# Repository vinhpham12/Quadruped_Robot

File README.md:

# Quadruped_Robot
A custom-designed 12-DOF quadruped robot platform featuring a modular 3D-printed chassis and a dedicated embedded controller board.

## Project Structure

* **hardware/**: 
  * `cad/`: Mechanical assembly, STEP files, and 3D printable STL files (SolidWorks).
  * `pcb/`: Custom mainboard schematics, PCB layout, and gerber files (KiCad).

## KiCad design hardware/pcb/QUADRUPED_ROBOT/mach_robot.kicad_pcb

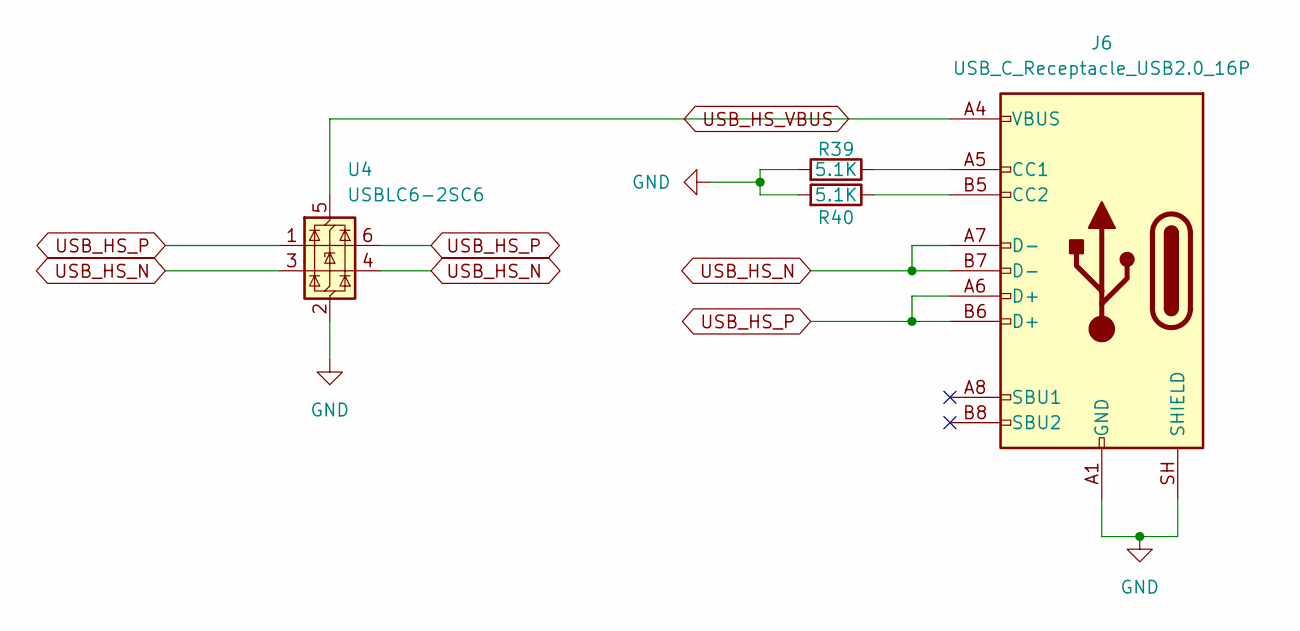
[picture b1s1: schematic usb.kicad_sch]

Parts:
J6: USB_C_Receptacle_USB2.0_16P; USB_C_Receptacle_Amphenol_12401948E412A
R39, R40: 5.1K; R_0805_2012Metric
U4: USBLC6-2SC6; SOT-23-6

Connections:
GND: J6.A1 (GND), J6.A12 (GND), J6.B1 (GND), J6.B12 (GND), J6.SH (SHIELD), R39.2, R40.2, U4.2 (GND); also elsewhere on the board
unnamed: J6.A5 (CC1), R39.1
unnamed: J6.B5 (CC2), R40.1
USB_HS_N: J6.A7 (D-), J6.B7 (D-), U4.3 (I/O2), U4.4 (I/O2); also elsewhere on the board
USB_HS_P: J6.A6 (D+), J6.B6 (D+), U4.1 (I/O1), U4.6 (I/O1); also elsewhere on the board
USB_HS_VBUS: J6.A4 (VBUS), J6.A9 (VBUS), J6.B4 (VBUS), J6.B9 (VBUS), U4.5 (VBUS); also elsewhere on the board

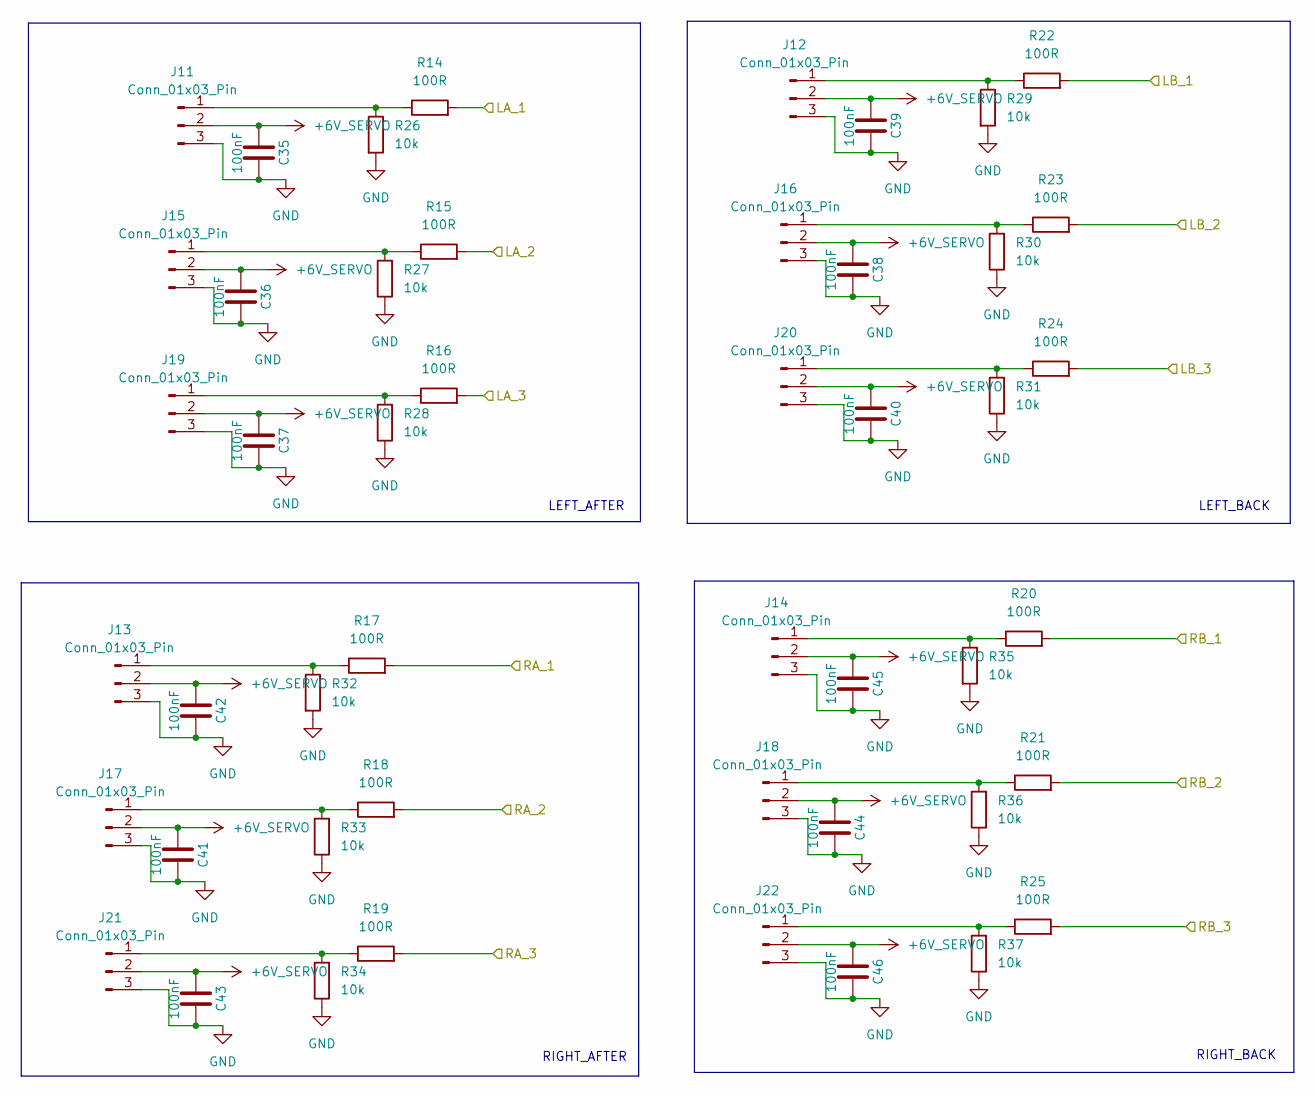
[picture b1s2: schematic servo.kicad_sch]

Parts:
C35, C36, C37, C38, C39, C40, C41, C42, C43, C44, C45, C46: 100nF; C_0805_2012Metric
J11, J12, J13, J14, J15, J16, J17, J18, J19, J20, J21, J22: Conn_01x03_Pin; PinHeader_1x03_P2.54mm_Vertical
R14, R15, R16, R17, R18, R19, R20, R21, R22, R23, R24, R25: 100R; R_0805_2012Metric
R26, R27, R28, R29, R30, R31, R32, R33, R34, R35, R36, R37: 10k; R_0805_2012Metric

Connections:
/chip/LA_1: R14.2; also elsewhere on the board
/chip/LA_2: R15.2; also elsewhere on the board
/chip/LA_3: R16.2; also elsewhere on the board
/chip/LB_1: R22.2; also elsewhere on the board
/chip/LB_2: R23.2; also elsewhere on the board
/chip/LB_3: R24.2; also elsewhere on the board
/chip/RA_1: R17.2; also elsewhere on the board
/chip/RA_2: R18.2; also elsewhere on the board
/chip/RA_3: R19.2; also elsewhere on the board
/chip/RB_1: R20.2; also elsewhere on the board
/chip/RB_2: R21.2; also elsewhere on the board
/chip/RB_3: R25.2; also elsewhere on the board
GND: C35.1, C36.1, C37.1, C38.1, C39.1, C40.1, C41.1, C42.1, C43.1, C44.1, C45.1, C46.1, J11.3, J12.3, J13.3, J14.3, J15.3, J16.3, J17.3, J18.3, J19.3, J20.3, J21.3, J22.3, R26.2, R27.1, R28.1, R29.2, R30.1, R31.1, R32.2, R33.1, R34.1, R35.2, R36.1, R37.1; also elsewhere on the board
unnamed: J11.1, R14.1, R26.1
unnamed: J12.1, R22.1, R29.1
unnamed: J13.1, R17.1, R32.1
unnamed: J14.1, R20.1, R35.1
unnamed: J15.1, R15.1, R27.2
unnamed: J16.1, R23.1, R30.2
unnamed: J17.1, R18.1, R33.2
unnamed: J18.1, R21.1, R36.2
unnamed: J19.1, R16.1, R28.2
unnamed: J20.1, R24.1, R31.2
unnamed: J21.1, R19.1, R34.2
unnamed: J22.1, R25.1, R37.2

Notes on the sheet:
LEFT_BACK
RIGHT_BACK
LEFT_AFTER
RIGHT_AFTER

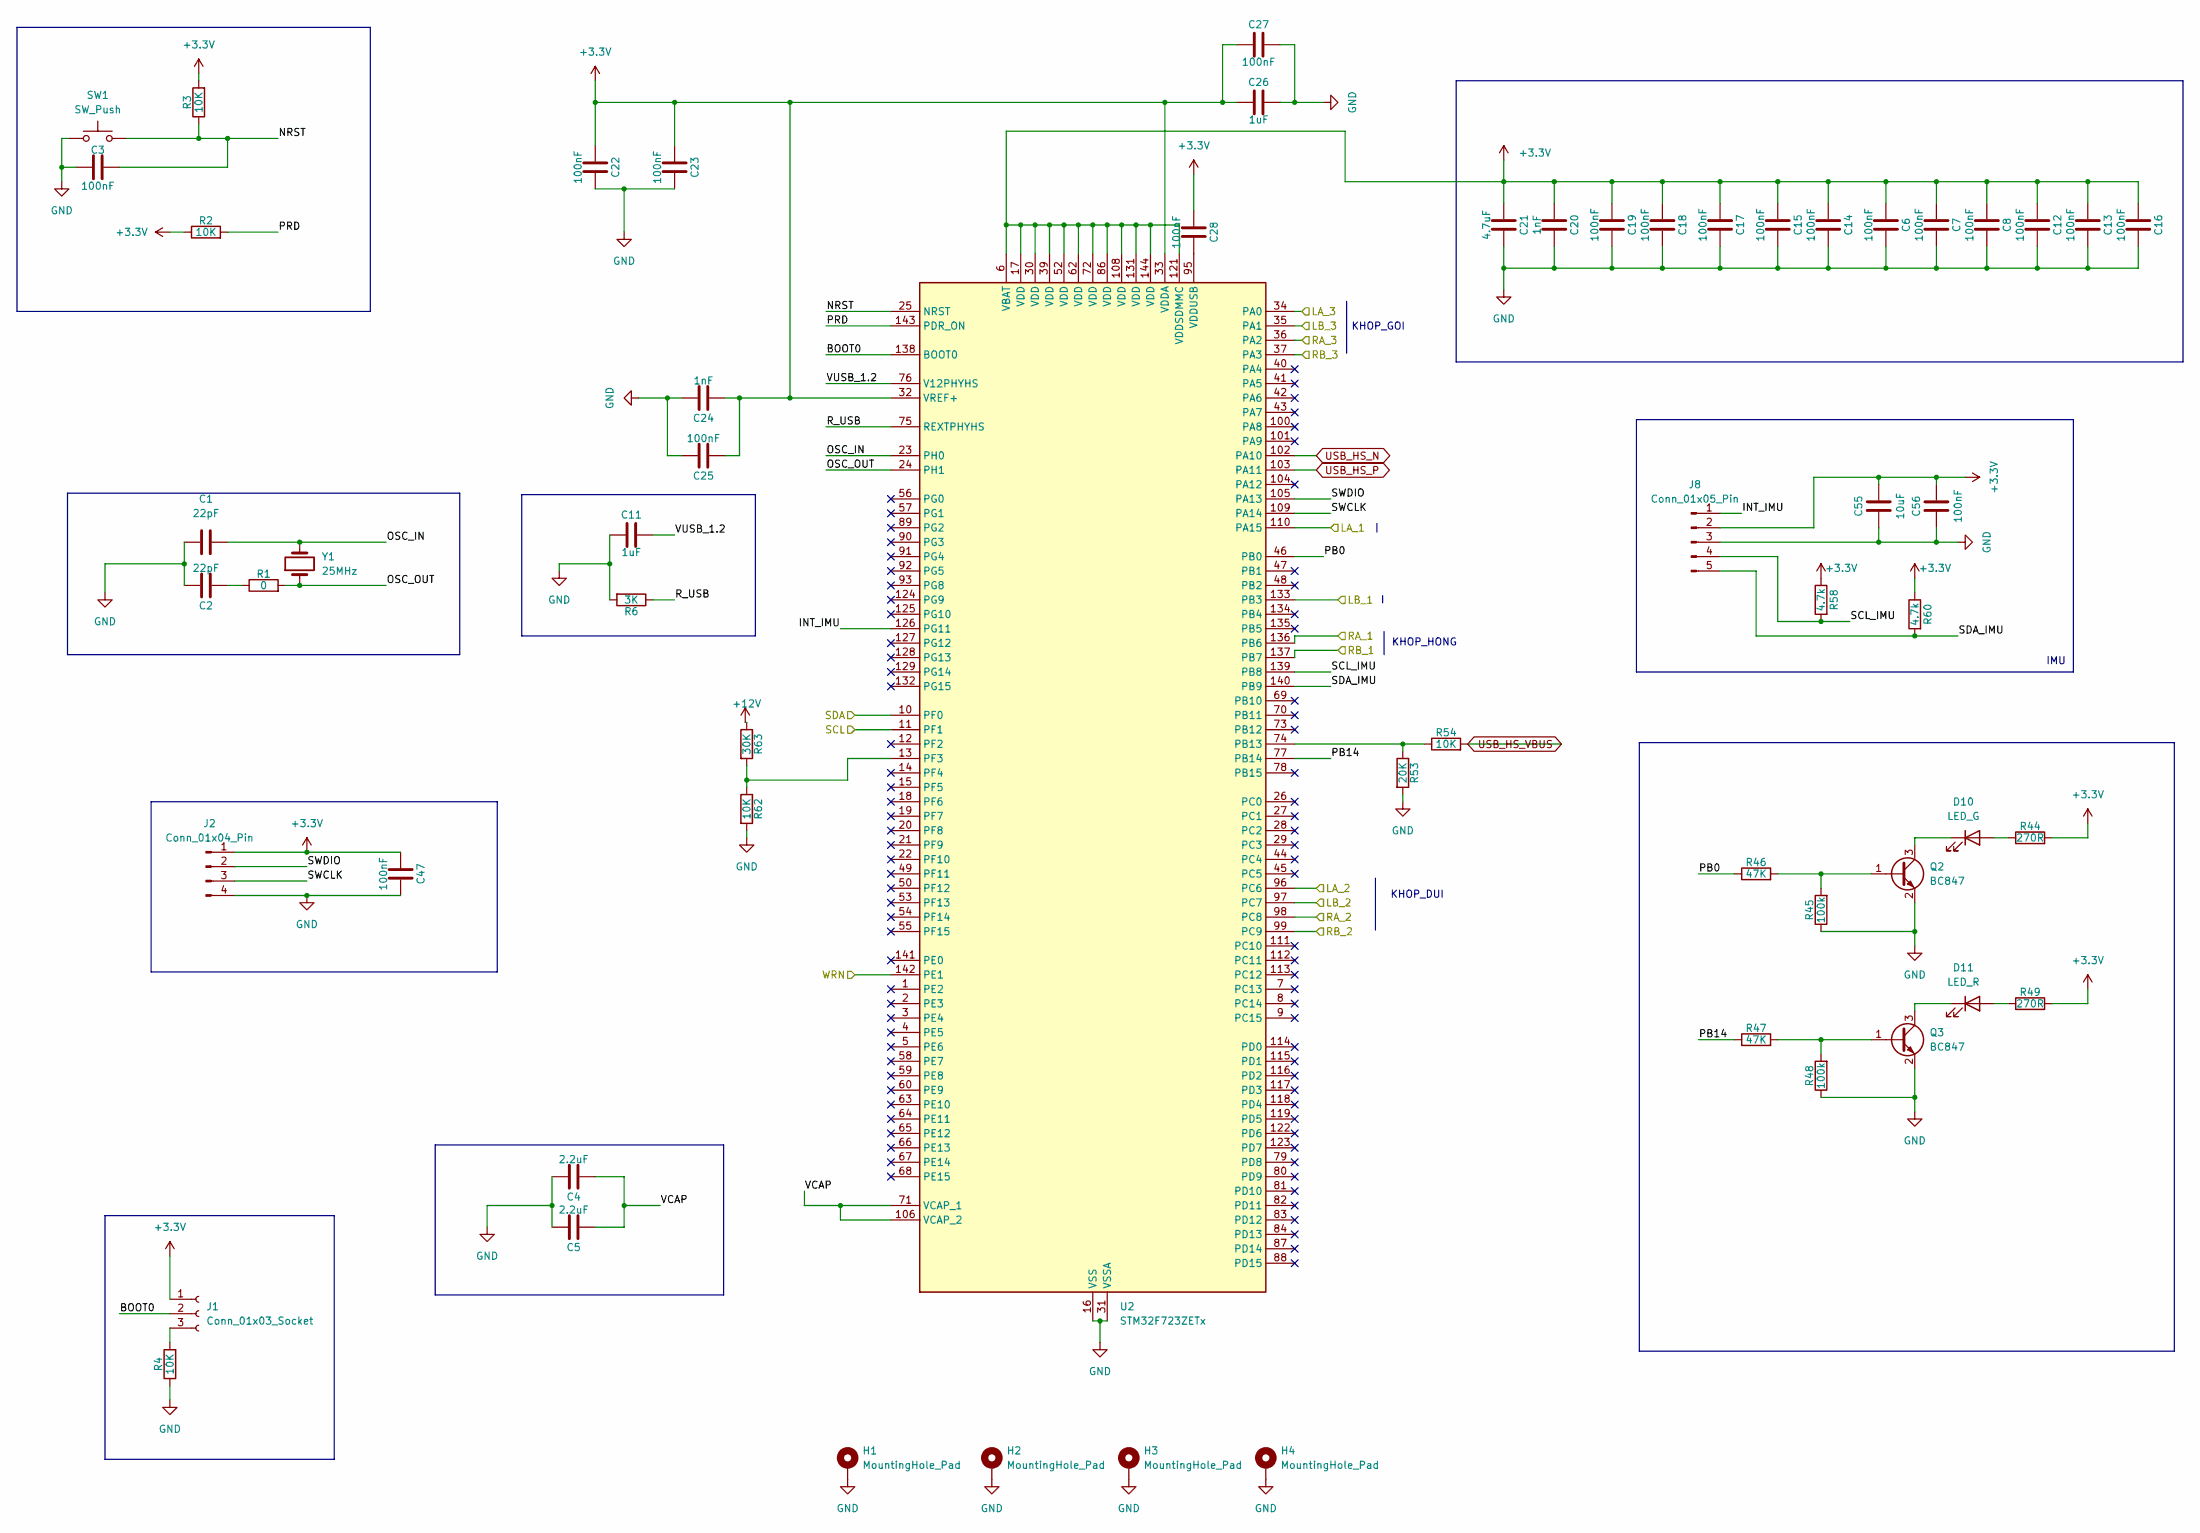
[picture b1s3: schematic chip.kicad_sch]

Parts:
C1, C2: 22pF; C_0805_2012Metric
C3, C6, C7, C8, C12, C13, C14, C15, C16, C17, C18, C19, C22, C23, C25, C27, C28, C47, C56: 100nF; C_0805_2012Metric
C4, C5: 2.2uF; C_0805_2012Metric
C11, C26: 1uF; C_0805_2012Metric
C20, C24: 1nF; C_0805_2012Metric
C21: 4.7uF; C_0805_2012Metric
C55: 10uF; C_0805_2012Metric
D10: LED_G; LED_0805_2012Metric
D11: LED_R; LED_0805_2012Metric
H1, H2, H3, H4: MountingHole_Pad; MountingHole_3.2mm_M3_Pad
J1: Conn_01x03_Socket; PinSocket_1x03_P2.54mm_Vertical
J2: Conn_01x04_Pin; PinSocket_1x04_P2.54mm_Vertical
J8: Conn_01x05_Pin; PinSocket_1x05_P2.54mm_Vertical
Q2, Q3: BC847; SOT-23
R1: 0; R_0805_2012Metric
R2, R3, R4, R54, R62: 10K; R_0805_2012Metric
R6: 3K; R_0805_2012Metric
R44, R49: 270R; R_0805_2012Metric
R45, R48: 100k; R_0805_2012Metric
R46, R47: 47K; R_0805_2012Metric
R53: 20K; R_0805_2012Metric
R58, R60: 4.7k; R_0805_2012Metric
R63: 30K; R_0805_2012Metric
SW1: SW_Push; SW_SMD_3x6mm
U2: STM32F723ZETx; LQFP-144_20x20mm_P0.5mm
Y1: 25MHz; Crystal_HC49-U_Vertical

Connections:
+3.3V: C6.2, C7.2, C8.2, C12.2, C13.2, C14.2, C15.2, C16.2, C17.2, C18.2, C19.2, C20.2, C21.2, C22.2, C23.2, C24.2, C25.2, C26.2, C27.2, C28.2, C47.2, C55.2, C56.2, J1.1, J2.1, J8.2, R2.1, R3.2, R44.2, R49.2, R58.1, R60.1, U2.6 (VBAT), U2.17 (VDD), U2.30 (VDD), U2.32 (VREF+), U2.33 (VDDA), U2.39 (VDD), U2.52 (VDD), U2.62 (VDD), U2.72 (VDD), U2.86 (VDD), U2.108 (VDD), U2.121 (VDDSDMMC), U2.131 (VDD), U2.144 (VDD); also elsewhere on the board
+12V: R63.1; also elsewhere on the board
/chip/BOOT0: J1.2, U2.138 (BOOT0)
/chip/INT_IMU: J8.1, U2.126 (PG11)
/chip/LA_1: U2.110 (PA15); also elsewhere on the board
/chip/LA_2: U2.96 (PC6); also elsewhere on the board
/chip/LA_3: U2.34 (PA0); also elsewhere on the board
/chip/LB_1: U2.133 (PB3); also elsewhere on the board
/chip/LB_2: U2.97 (PC7); also elsewhere on the board
/chip/LB_3: U2.35 (PA1); also elsewhere on the board
/chip/NRST: C3.2, R3.1, SW1.2, U2.25 (NRST)
/chip/OSC_IN: C1.2, U2.23 (PH0), Y1.2
/chip/OSC_OUT: R1.2, U2.24 (PH1), Y1.1
/chip/PB0: R46.1, U2.46 (PB0)
/chip/PB14: R47.1, U2.77 (PB14)
/chip/PRD: R2.2, U2.143 (PDR_ON)
/chip/RA_1: U2.136 (PB6); also elsewhere on the board
/chip/RA_2: U2.98 (PC8); also elsewhere on the board
/chip/RA_3: U2.36 (PA2); also elsewhere on the board
/chip/RB_1: U2.137 (PB7); also elsewhere on the board
/chip/RB_2: U2.99 (PC9); also elsewhere on the board
/chip/RB_3: U2.37 (PA3); also elsewhere on the board
/chip/R_USB: R6.1, U2.75 (REXTPHYHS)
/chip/SCL: U2.11 (PF1); also elsewhere on the board
/chip/SCL_IMU: J8.4, R58.2, U2.139 (PB8)
/chip/SDA: U2.10 (PF0); also elsewhere on the board
/chip/SDA_IMU: J8.5, R60.2, U2.140 (PB9)
/chip/SWCLK: J2.3, U2.109 (PA14)
/chip/SWDIO: J2.2, U2.105 (PA13)
/chip/VCAP: C4.2, C5.2, U2.71 (VCAP_1), U2.106 (VCAP_2)
/chip/VUSB_1.2: C11.1, U2.76 (V12PHYHS)
/chip/WRN: U2.142 (PE1); also elsewhere on the board
GND: C1.1, C2.1, C3.1, C4.1, C5.1, C6.1, C7.1, C8.1, C11.2, C12.1, C13.1, C14.1, C15.1, C16.1, C17.1, C18.1, C19.1, C20.1, C21.1, C22.1, C23.1, C24.1, C25.1, C26.1, C27.1, C47.1, C55.1, C56.1, H1.1 (1_1), H2.1 (1_1), H3.1 (1_1), H4.1 (1_1), J2.4, J8.3, Q2.2 (E), Q3.2 (E), R4.1, R6.2, R45.1, R48.1, R53.2, R62.2, SW1.1, U2.16 (VSS), U2.31 (VSSA), U2.38 (VSS), U2.51 (VSS), U2.61 (VSS), U2.85 (VSS), U2.94 (VSS), U2.107 (VSS), U2.120 (VSS), U2.130 (VSS); also elsewhere on the board
unnamed: C2.2, R1.1
unnamed: D10.2 (A), R44.1
unnamed: D10.1 (K), Q2.3 (C)
unnamed: D11.2 (A), R49.1
unnamed: D11.1 (K), Q3.3 (C)
unnamed: J1.3, R4.2
unnamed: Q2.1 (B), R45.2, R46.2
unnamed: Q3.1 (B), R47.2, R48.2
unnamed: R53.1, R54.1, U2.74 (PB13)
unnamed: R62.1, R63.2, U2.13 (PF3)
unnamed: C28.1, U2.95 (VDDUSB)
USB_HS_N: U2.102 (PA10); also elsewhere on the board
USB_HS_P: U2.103 (PA11); also elsewhere on the board
USB_HS_VBUS: R54.2; also elsewhere on the board

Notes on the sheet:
IMU
KHOP_HONG
KHOP_DUI
KHOP_GOI

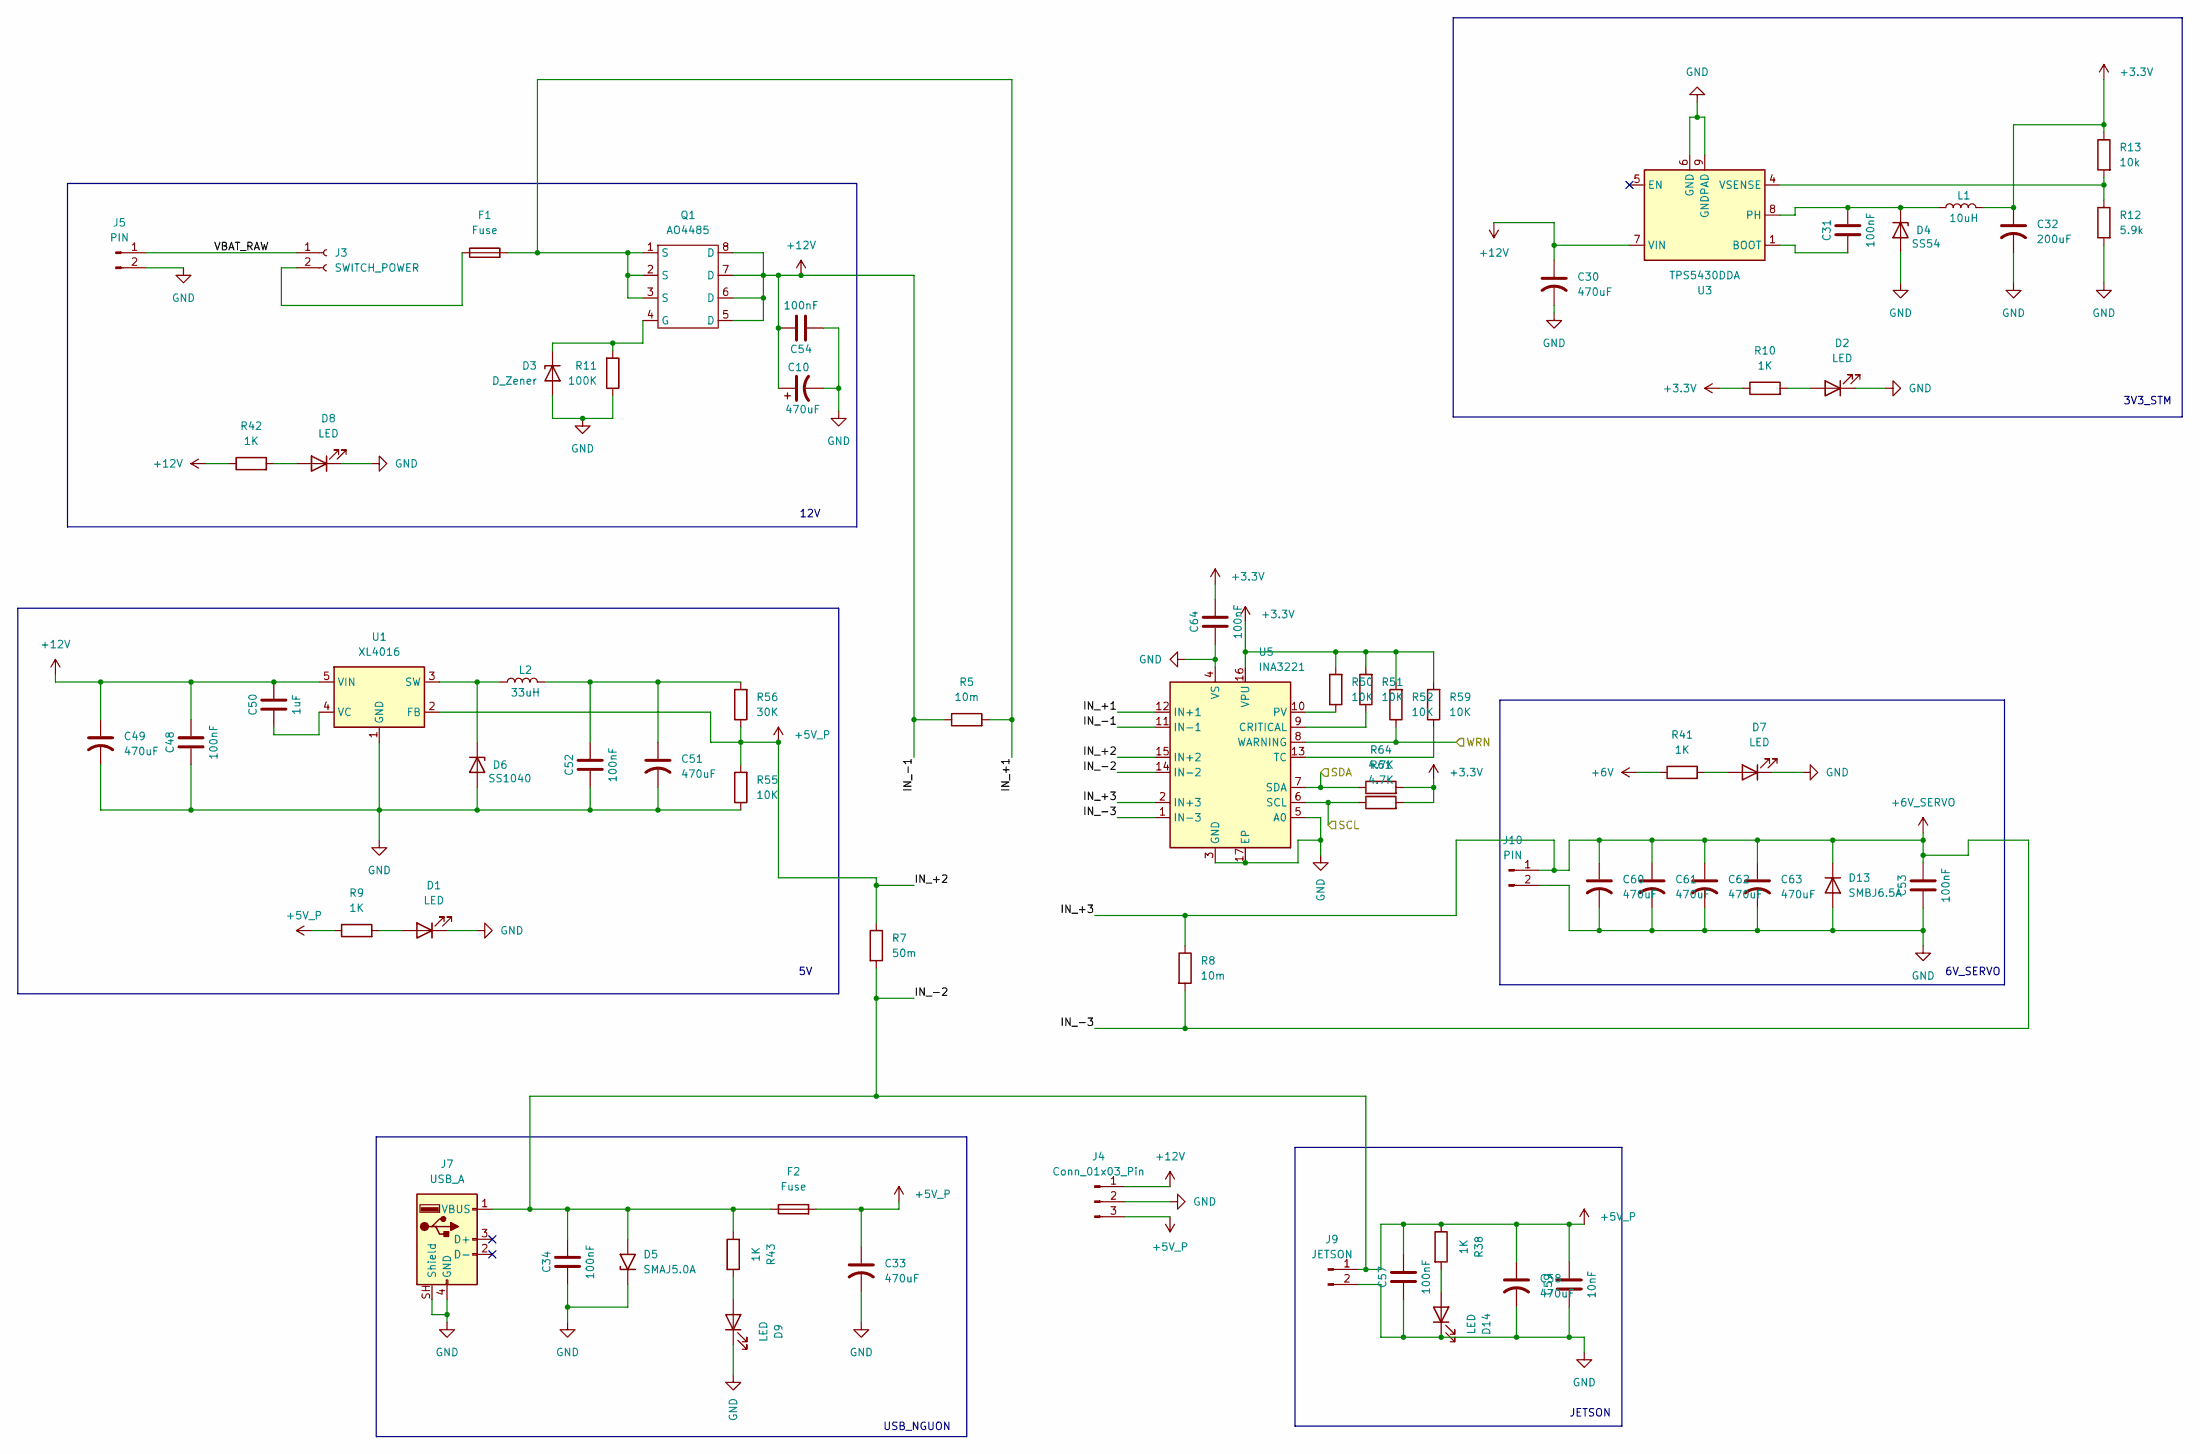
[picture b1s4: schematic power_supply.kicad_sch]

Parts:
C10: 470uF; CP_Radial_D10.0mm_P5.00mm
C30, C49, C51: 470uF; CP_Elec_8x10
C31, C34, C48, C52, C53, C54, C57, C64: 100nF; C_0805_2012Metric
C32: 200uF; CP_EIA-7343-31_Kemet-D_HandSolder
C33, C58, C60, C61, C62, C63: 470uF; CP_EIA-7343-31_Kemet-D_HandSolder
C50: 1uF; C_0805_2012Metric
C59: 10nF; C_0805_2012Metric
D1, D2, D7, D8, D9, D14: LED; LED_0805_2012Metric
D3: D_Zener; D_0805_2012Metric
D4: SS54; D_SMC
D5: SMAJ5.0A; D_SMA
D6: SS1040; D_SMC
D13: SMBJ6.5A; D_SMB
F1, F2: Fuse; Fuseholder_Littelfuse_100_series_5x20mm
J3: SWITCH_POWER; PinHeader_1x02_P2.54mm_Vertical
J4: Conn_01x03_Pin; PinHeader_1x03_P2.54mm_Vertical
J5, J10: PIN; TerminalBlock_Phoenix_MKDS-1,5-2-5.08_1x02_P5.08mm_Horizont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
J7: USB_A; USB_A_Molex_67643_Horizontal
J9: JETSON; TerminalBlock_Phoenix_MKDS-1,5-2-5.08_1x02_P5.08mm_Horizont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
L1: 10uH; L_12x12mm_H6mm
L2: 33uH; L_12x12mm_H6mm
Q1: AO4485; SOIC-8_3.9x4.9mm_P1.27mm
R5, R8: 10m; R_2512_6332Metric
R7: 50m; R_2512_6332Metric
R9, R10, R38, R41, R42, R43: 1K; R_0805_2012Metric
R11: 100K; R_0805_2012Metric
R12: 5.9k; R_0805_2012Metric
R13: 10k; R_0805_2012Metric
R50, R51, R52, R55, R59: 10K; R_0805_2012Metric
R56: 30K; R_0805_2012Metric
R61, R64: 4.7K; R_0805_2012Metric
U1: XL4016; TO-263-5_TabPin3
U3: TPS5430DDA; TI_SO-PowerPAD-8_ThermalVias
U5: INA3221; Texas_RGV0016A_VQFN-16-1EP_4x4mm_P0.65mm_EP2.1x2.1mm

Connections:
+3.3V: C32.1, C64.2, L1.1, R10.1, R13.1, R50.2, R51.2, R52.2, R59.2, R61.2, R64.2, U5.16 (VPU); also elsewhere on the board
+5V_P: C33.1, C34.2, C57.2, C58.1, C59.2, D5.2 (A2), F2.1, F2.2, J4.3, J7.1 (VBUS), J9.1, R7.1, R7.2, R9.1, R38.1, R43.1, R55.2, R56.1, U1.2 (FB), U5.14 (IN-2), U5.15 (IN+2)
+12V: C10.1, C30.1, C48.2, C49.1, C50.2, C54.2, J4.1, Q1.5 (D), Q1.6 (D), Q1.7 (D), Q1.8 (D), R5.1, R42.1, U1.5 (VIN), U3.7 (VIN), U5.11 (IN-1); also elsewhere on the board
/chip/SCL: R61.1, U5.6 (SCL); also elsewhere on the board
/chip/SDA: R64.1, U5.7 (SDA); also elsewhere on the board
/chip/WRN: R52.1, U5.8 (WARNING); also elsewhere on the board
/power supply/IN_+1: F1.2, Q1.1 (S), Q1.2 (S), Q1.3 (S), R5.2, U5.12 (IN+1)
/power supply/VBAT_RAW: J3.1, J5.1
GND: C10.2, C30.2, C32.2, C33.2, C34.1, C48.1, C49.2, C51.2, C52.1, C53.1, C54.1, C57.1, C58.2, C59.1, C60.2, C61.2, C62.2, C63.2, C64.1, D1.1 (K), D2.1 (K), D3.2 (A), D4.2 (A), D5.1 (A1), D6.2 (A), D7.1 (K), D8.1 (K), D9.1 (K), D13.2 (A), D14.1 (K), J4.2, J5.2, J7.4 (GND), J7.SH (Shield), J9.2, J10.2, R11.1, R12.2, R55.1, U1.1 (GND), U3.6 (GND), U3.9 (GNDPAD), U5.3 (GND), U5.4 (VS), U5.5 (A0), U5.17 (EP); also elsewhere on the board
unnamed: C51.1, C52.2, L2.1, R56.2
unnamed: D1.2 (A), R9.2
unnamed: D2.2 (A), R10.2
unnamed: D3.1 (K), Q1.4 (G), R11.2
unnamed: C31.2, D4.1 (K), L1.2, U3.8 (PH)
unnamed: D6.1 (K), L2.2, U1.3 (SW)
unnamed: D7.2 (A), R41.2
unnamed: D8.2 (A), R42.2
unnamed: D9.2 (A), R43.2
unnamed: D14.2 (A), R38.2
unnamed: F1.1, J3.2
unnamed: C50.1, U1.4 (VC)
unnamed: C31.1, U3.1 (BOOT)
unnamed: R12.1, R13.2, U3.4 (VSENSE)
unnamed: R51.1, U5.9 (CRITICAL)
unnamed: R50.1, U5.10 (PV)
unnamed: R59.1, U5.13 (TC)

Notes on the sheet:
12V
3V3_STM
6V_SERVO
JETSON
USB_NGUON

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
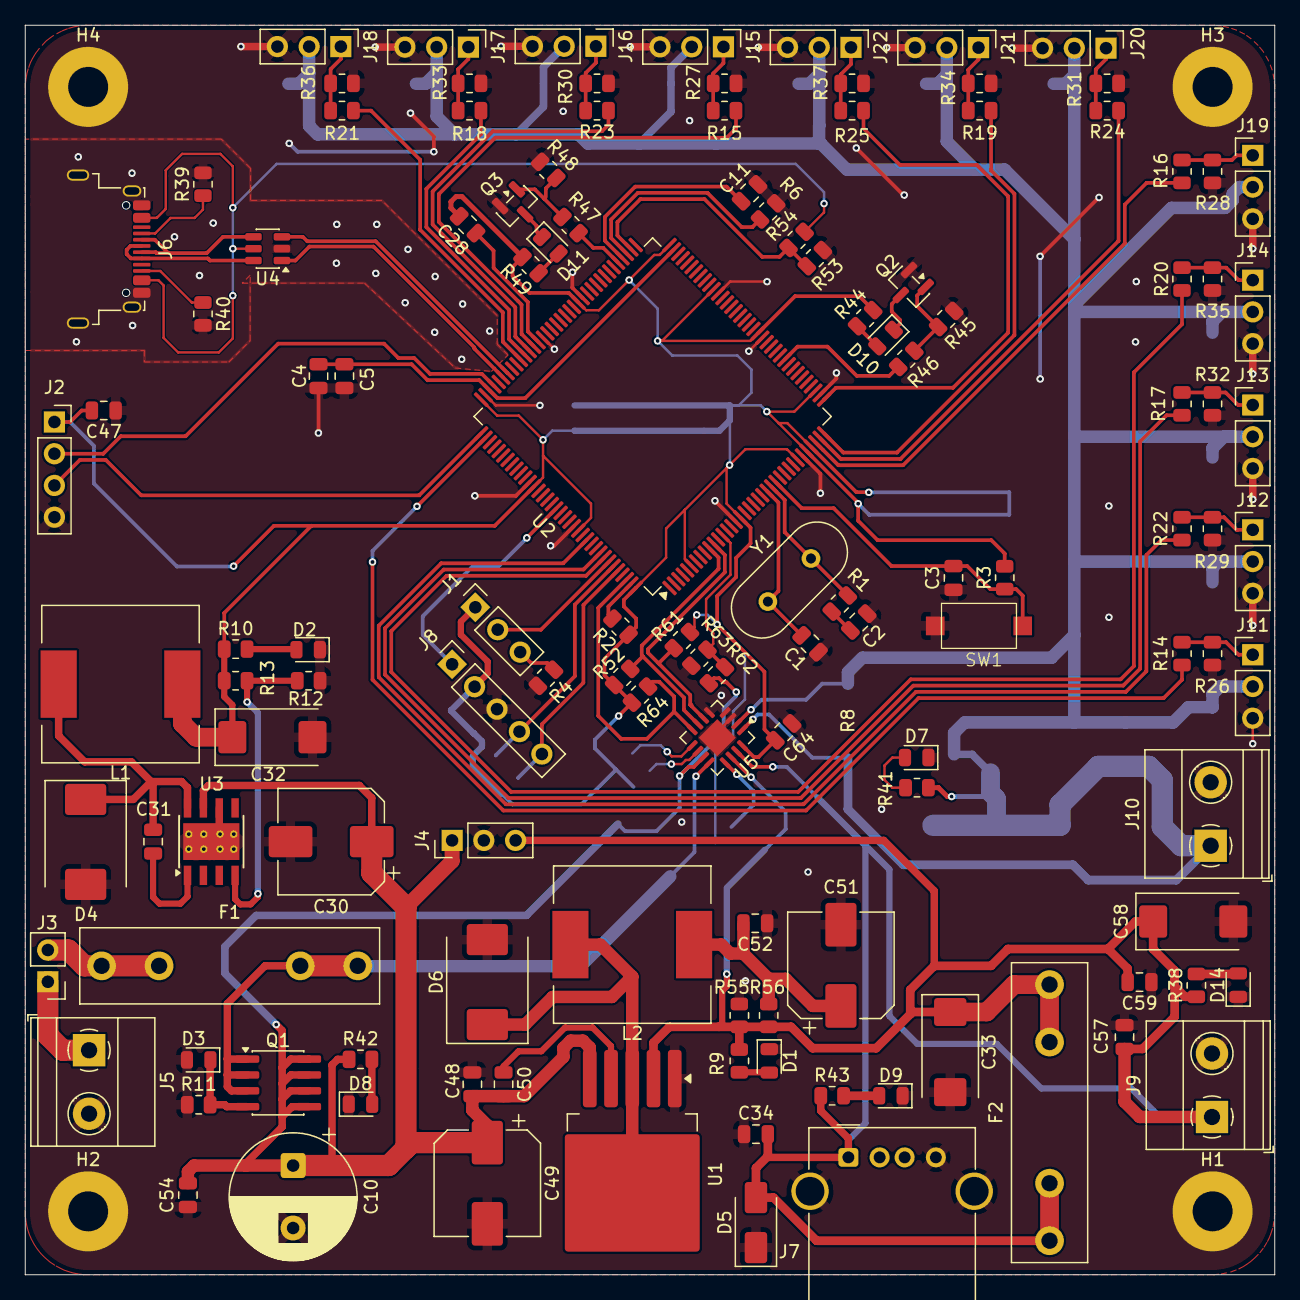
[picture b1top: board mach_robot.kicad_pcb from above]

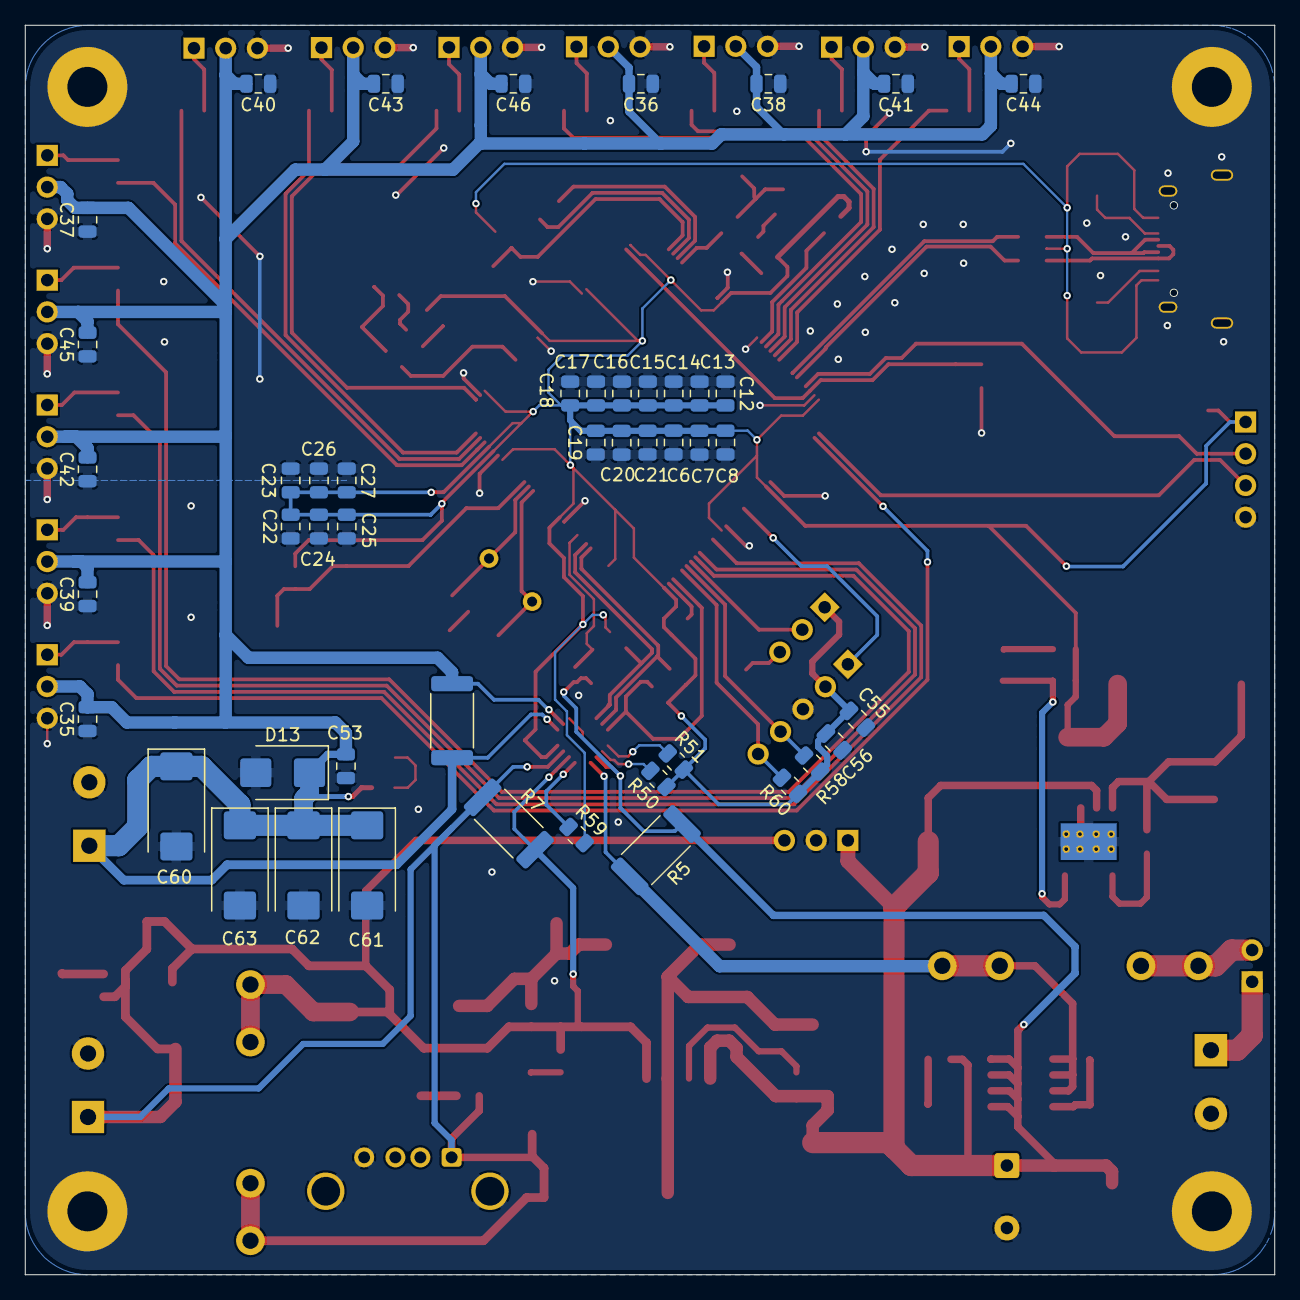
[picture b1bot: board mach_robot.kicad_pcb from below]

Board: 2 copper layers, 100.0 x 100.0 mm, 178 parts (47 on the bottom side), 82 nets.
